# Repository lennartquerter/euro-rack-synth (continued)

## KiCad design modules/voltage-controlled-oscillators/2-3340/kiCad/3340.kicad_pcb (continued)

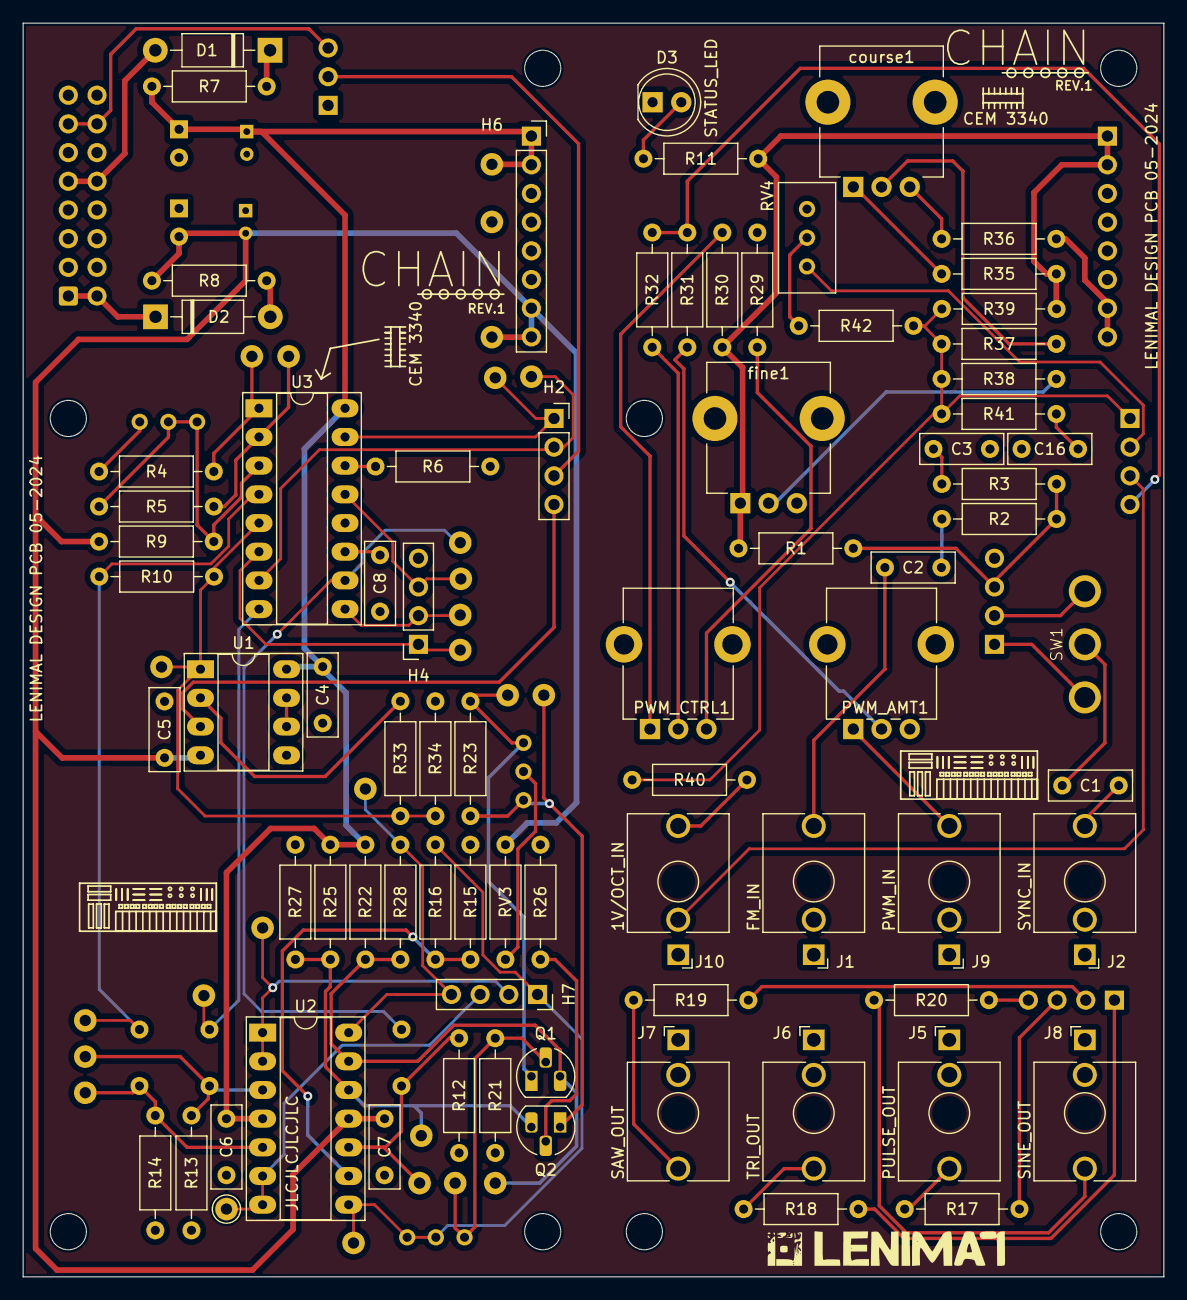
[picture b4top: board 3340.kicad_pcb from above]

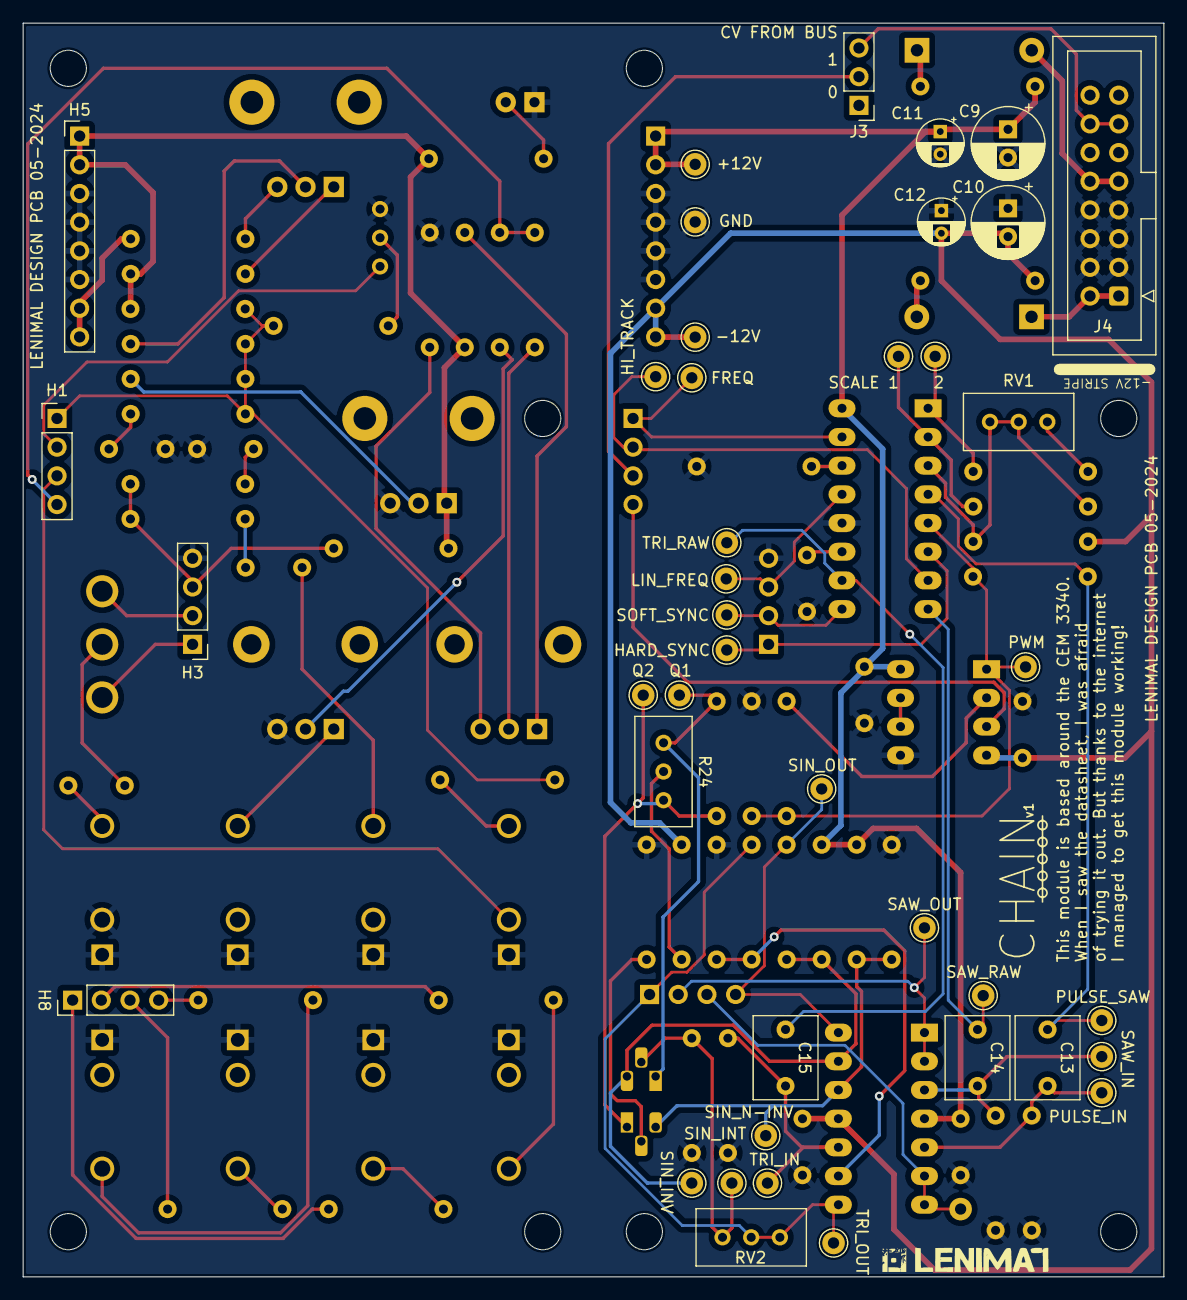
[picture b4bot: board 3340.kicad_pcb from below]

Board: 2 copper layers, 101.0 x 111.0 mm, 127 parts (41 on the bottom side), 75 nets.

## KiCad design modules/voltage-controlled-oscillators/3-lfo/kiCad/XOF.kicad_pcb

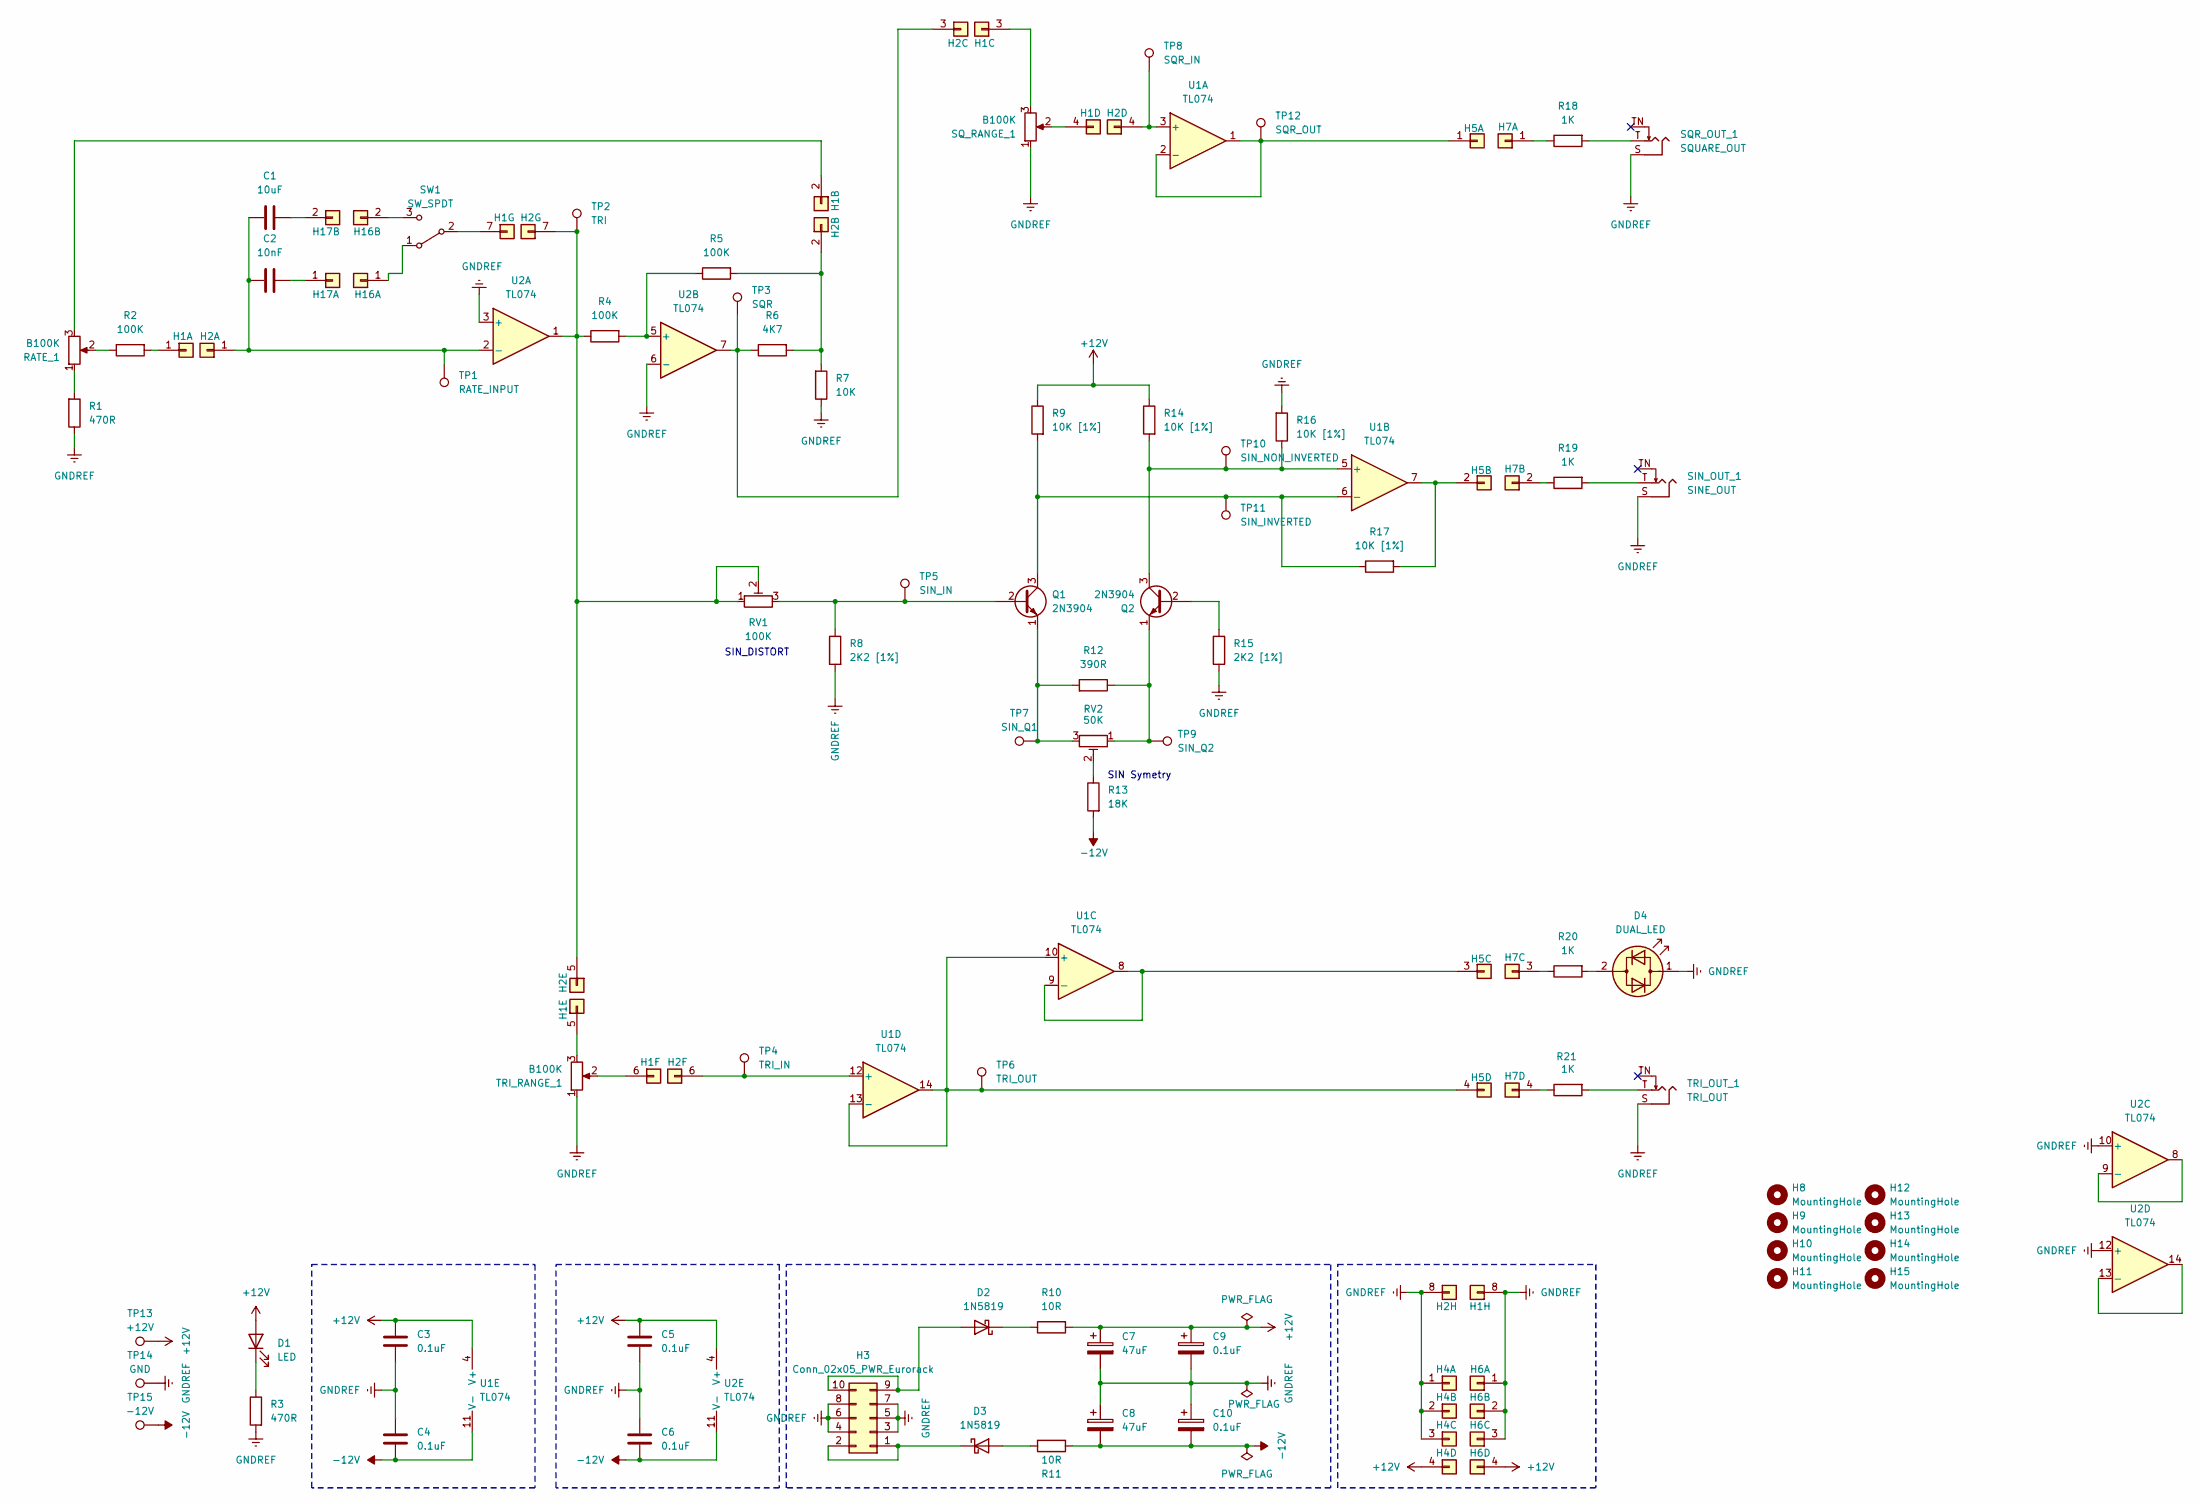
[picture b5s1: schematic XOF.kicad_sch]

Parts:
C1: 10uF; C_RECT_MKT_1uF
C2: 10nF; C_RECT_MKT_1uF
C3, C4, C5, C6: 0.1uF; C_Disc_D5.0mm_W2.5mm_P5.00mm
C7, C8: 47uF; CP_Radial_D6.3mm_P2.50mm
C9, C10: 0.1uF; CP_Radial_D4.0mm_P2.00mm
D1: LED; LED_D5.0mm (center Aligned)
D2, D3: 1N5819; D_DO-41_SOD81_P10.16mm_Horizontal
D4: DUAL_LED; LED_D5.0mm (center Aligned)
H1: PinHeader_01x08; PinHeader_1x08_P2.54mm_Vertical
H2: PinSocket_01x08; PinSocket_1x08_P2.54mm_Vertical
H3: Conn_02x05_PWR_Eurorack; IDC-Header_2x05_P2.54mm_Vertical
H4, H7: PinHeader_01x04; PinHeader_1x04_P2.54mm_Vertical
H5, H6: PinSocket_01x04; PinSocket_1x04_P2.54mm_Vertical
H8, H9, H10, H11, H12, H13, H14, H15: MountingHole; MountingHole_3.2mm_M3
H16: PinHeader_01x02; PinHeader_1x02_P2.54mm_Vertical
H17: PinSocket_01x02; PinSocket_1x02_P2.54mm_Vertical
Q1, Q2: 2N3904; TO-92_HandSolder
R1, R3: 470R; R_Default (DIN0207)
R2, R4, R5: 100K; R_Default (DIN0207)
R6: 4K7; R_Default (DIN0207)
R7: 10K; R_Default (DIN0207)
R8, R15: 2K2 [1%]; R_Default (DIN0207)
R9, R14, R16, R17: 10K [1%]; R_Default (DIN0207)
R10, R11: 10R; R_Default (DIN0207)
R12: 390R; R_Default (DIN0207)
R13: 18K; R_Default (DIN0207)
R18, R19, R20, R21: 1K; R_Default (DIN0207)
RATE_1: B100K; Potentiometer_TT_P0915N
RV1: 100K; Potentiometer_Bourns_3296W_Vertical
RV2: 50K; Potentiometer_Bourns_3296W_Vertical
SIN_OUT_1: SINE_OUT; Jack_3.5mm_QingPu_WQP-PJ398SM_Vertical_CircularHoles
SQR_OUT_1: SQUARE_OUT; Jack_3.5mm_QingPu_WQP-PJ398SM_Vertical_CircularHoles
SQ_RANGE_1: B100K; Potentiometer_TT_P0915N
SW1: SW_SPDT; SW_default
TP1: RATE_INPUT; Pin_D1.0mm_L10.0mm
TP2: TRI; Pin_D1.0mm_L10.0mm
TP3: SQR; Pin_D1.0mm_L10.0mm
TP4: TRI_IN; Pin_D1.0mm_L10.0mm
TP5: SIN_IN; Pin_D1.0mm_L10.0mm
TP6: TRI_OUT; Pin_D1.0mm_L10.0mm
TP7: SIN_Q1; Pin_D1.0mm_L10.0mm
TP8: SQR_IN; Pin_D1.0mm_L10.0mm
TP9: SIN_Q2; Pin_D1.0mm_L10.0mm
TP10: SIN_NON_INVERTED; Pin_D1.0mm_L10.0mm
TP11: SIN_INVERTED; Pin_D1.0mm_L10.0mm
TP12: SQR_OUT; Pin_D1.0mm_L10.0mm
TP13: +12V; Pin_D1.0mm_L10.0mm
TP14: GND; Pin_D1.0mm_L10.0mm
TP15: -12V; Pin_D1.0mm_L10.0mm
TRI_OUT_1: TRI_OUT; Jack_3.5mm_QingPu_WQP-PJ398SM_Vertical_CircularHoles
TRI_RANGE_1: B100K; Potentiometer_TT_P0915N
U1, U2: TL074; DIP-14_W7.62mm_Socket_LongPads

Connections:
+12V: C3.1, C5.1, C7.1, C9.1, D1.2 (A), H4.4, H6.4, R9.2, R10.1, R14.2, TP13.1, U1.4 (V+), U2.4 (V+)
-12V: C4.2, C6.2, C8.2, C10.2, R11.1, R13.1, TP15.1, U1.11 (V-), U2.11 (V-)
GNDREF: C3.2, C4.1, C5.2, C6.1, C7.2, C8.1, C9.2, C10.1, D4.1 (KA), H1.8, H2.8, H3.3, H3.4, H3.5, H3.6, H3.7, H3.8, H4.1, H4.2, H4.3, H6.1, H6.2, H6.3, R1.2, R3.1, R7.2, R8.1, R15.2, R16.1, SIN_OUT_1.S, SQR_OUT_1.S, SQ_RANGE_1.1, TP14.1, TRI_OUT_1.S, TRI_RANGE_1.1, U2.3 (+), U2.6 (-), U2.10 (+), U2.12 (+)
unnamed: D1.1 (K), R3.2
unnamed: D2.2 (A), H3.9, H3.10
unnamed: D2.1 (K), R10.2
unnamed: D3.2 (A), R11.2
unnamed: D3.1 (K), H3.1, H3.2
unnamed: D4.2 (AK), R20.1
unnamed: H1.1, R2.1
unnamed: H1.2, RATE_1.3
unnamed: H1.3, SQ_RANGE_1.3
unnamed: H1.4, SQ_RANGE_1.2
unnamed: H1.5, TRI_RANGE_1.3
unnamed: H1.6, TRI_RANGE_1.2
unnamed: H1.7, SW1.2 (B)
unnamed: C1.1, C2.1, H2.1 (Pin_3), TP1.1, U2.2 (-)
unnamed: H2.2, R5.1, R6.1, R7.1
unnamed: H2.3, R6.2, TP3.1, U2.7
unnamed: H2.4, TP8.1, U1.3 (+)
unnamed: H2.5, H2.7, R4.2, RV1.1, RV1.2, TP2.1, U2.1
unnamed: H2.6, TP4.1, U1.12 (+)
unnamed: H5.1, TP12.1, U1.1, U1.2 (-)
unnamed: H5.2, R17.1, U1.7
unnamed: H5.3, U1.8, U1.9 (-)
unnamed: H5.4, TP6.1, U1.10 (+), U1.13 (-), U1.14
unnamed: H7.1, R18.2
unnamed: H7.2, R19.2
unnamed: H7.3, R20.2
unnamed: H7.4, R21.2
unnamed: H16.1, SW1.1 (A)
unnamed: H16.2, SW1.3 (C)
unnamed: C2.2, H17.1
unnamed: C1.2, H17.2
unnamed: Q1.2 (B), R8.2, RV1.3, TP5.1
unnamed: Q1.3 (C), R9.1, R17.2, TP11.1, U1.6 (-)
unnamed: Q1.1 (E), R12.1, RV2.3, TP7.1
unnamed: Q2.2 (B), R15.1
unnamed: Q2.3 (C), R14.1, R16.2, TP10.1, U1.5 (+)
unnamed: Q2.1 (E), R12.2, RV2.1, TP9.1
unnamed: R1.1, RATE_1.1
unnamed: R2.2, RATE_1.2
unnamed: R13.2, RV2.2
unnamed: R18.1, SQR_OUT_1.T
unnamed: R19.1, SIN_OUT_1.T
unnamed: R21.1, TRI_OUT_1.T
unnamed: R4.1, R5.2, U2.5 (+)
unnamed: U2.8, U2.9 (-)
unnamed: U2.13 (-), U2.14

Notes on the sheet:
SIN Symetry
SIN_DISTORT

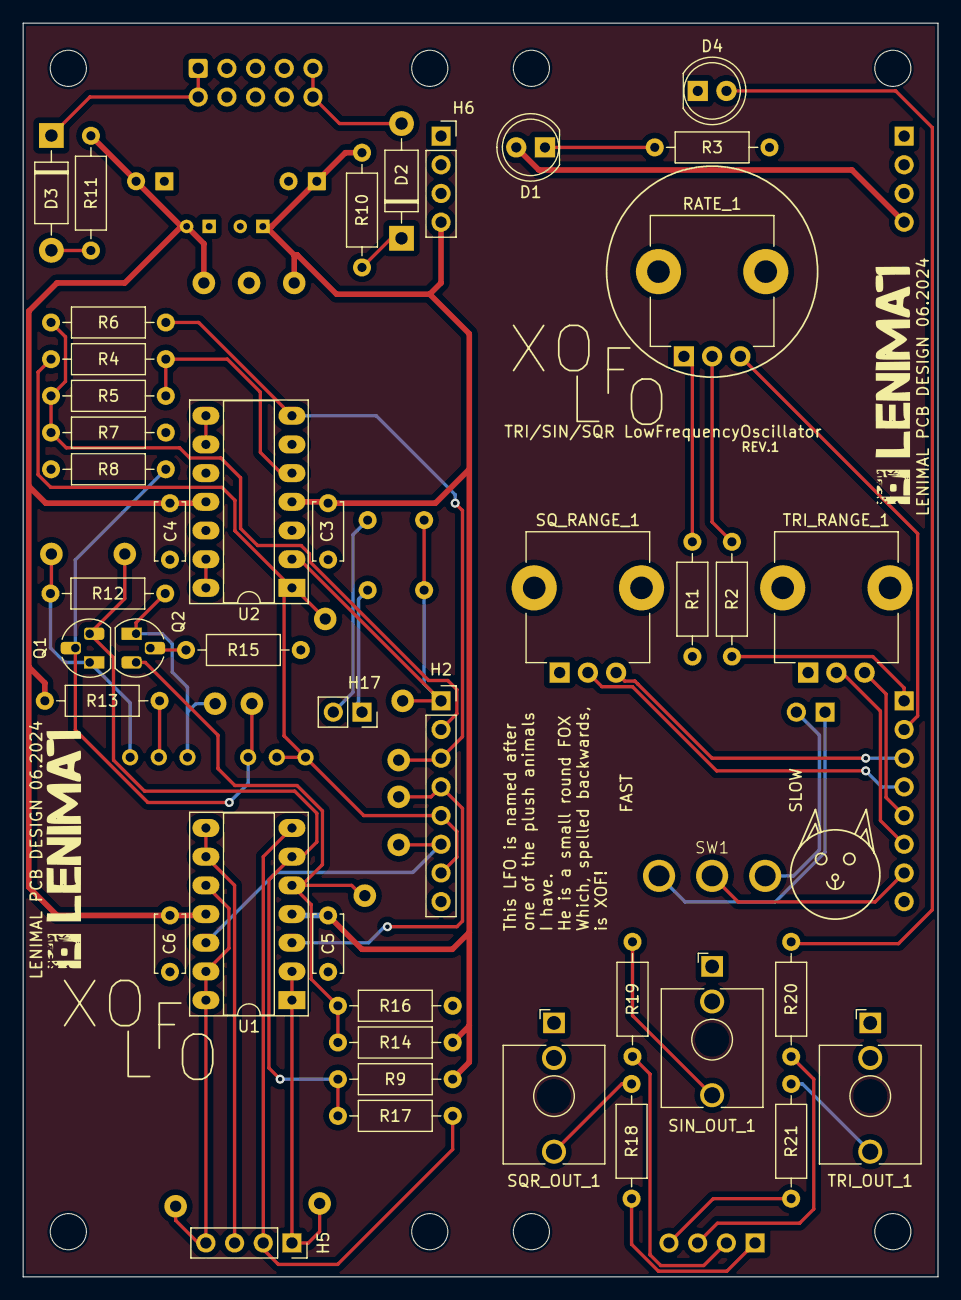
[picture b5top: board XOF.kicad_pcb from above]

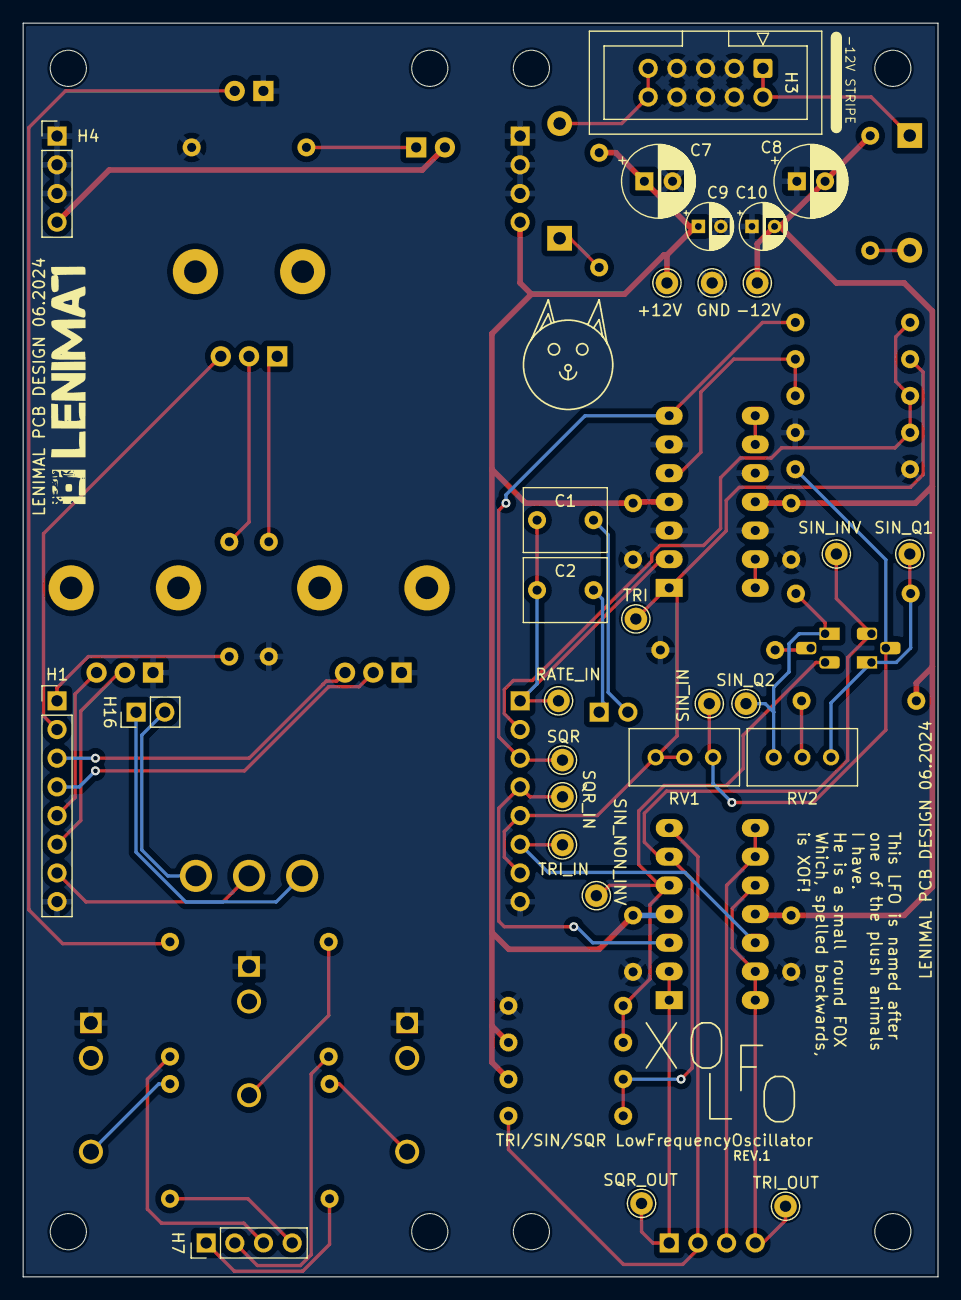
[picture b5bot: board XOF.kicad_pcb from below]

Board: 2 copper layers, 81.0 x 111.0 mm, 80 parts (28 on the bottom side), 49 nets.

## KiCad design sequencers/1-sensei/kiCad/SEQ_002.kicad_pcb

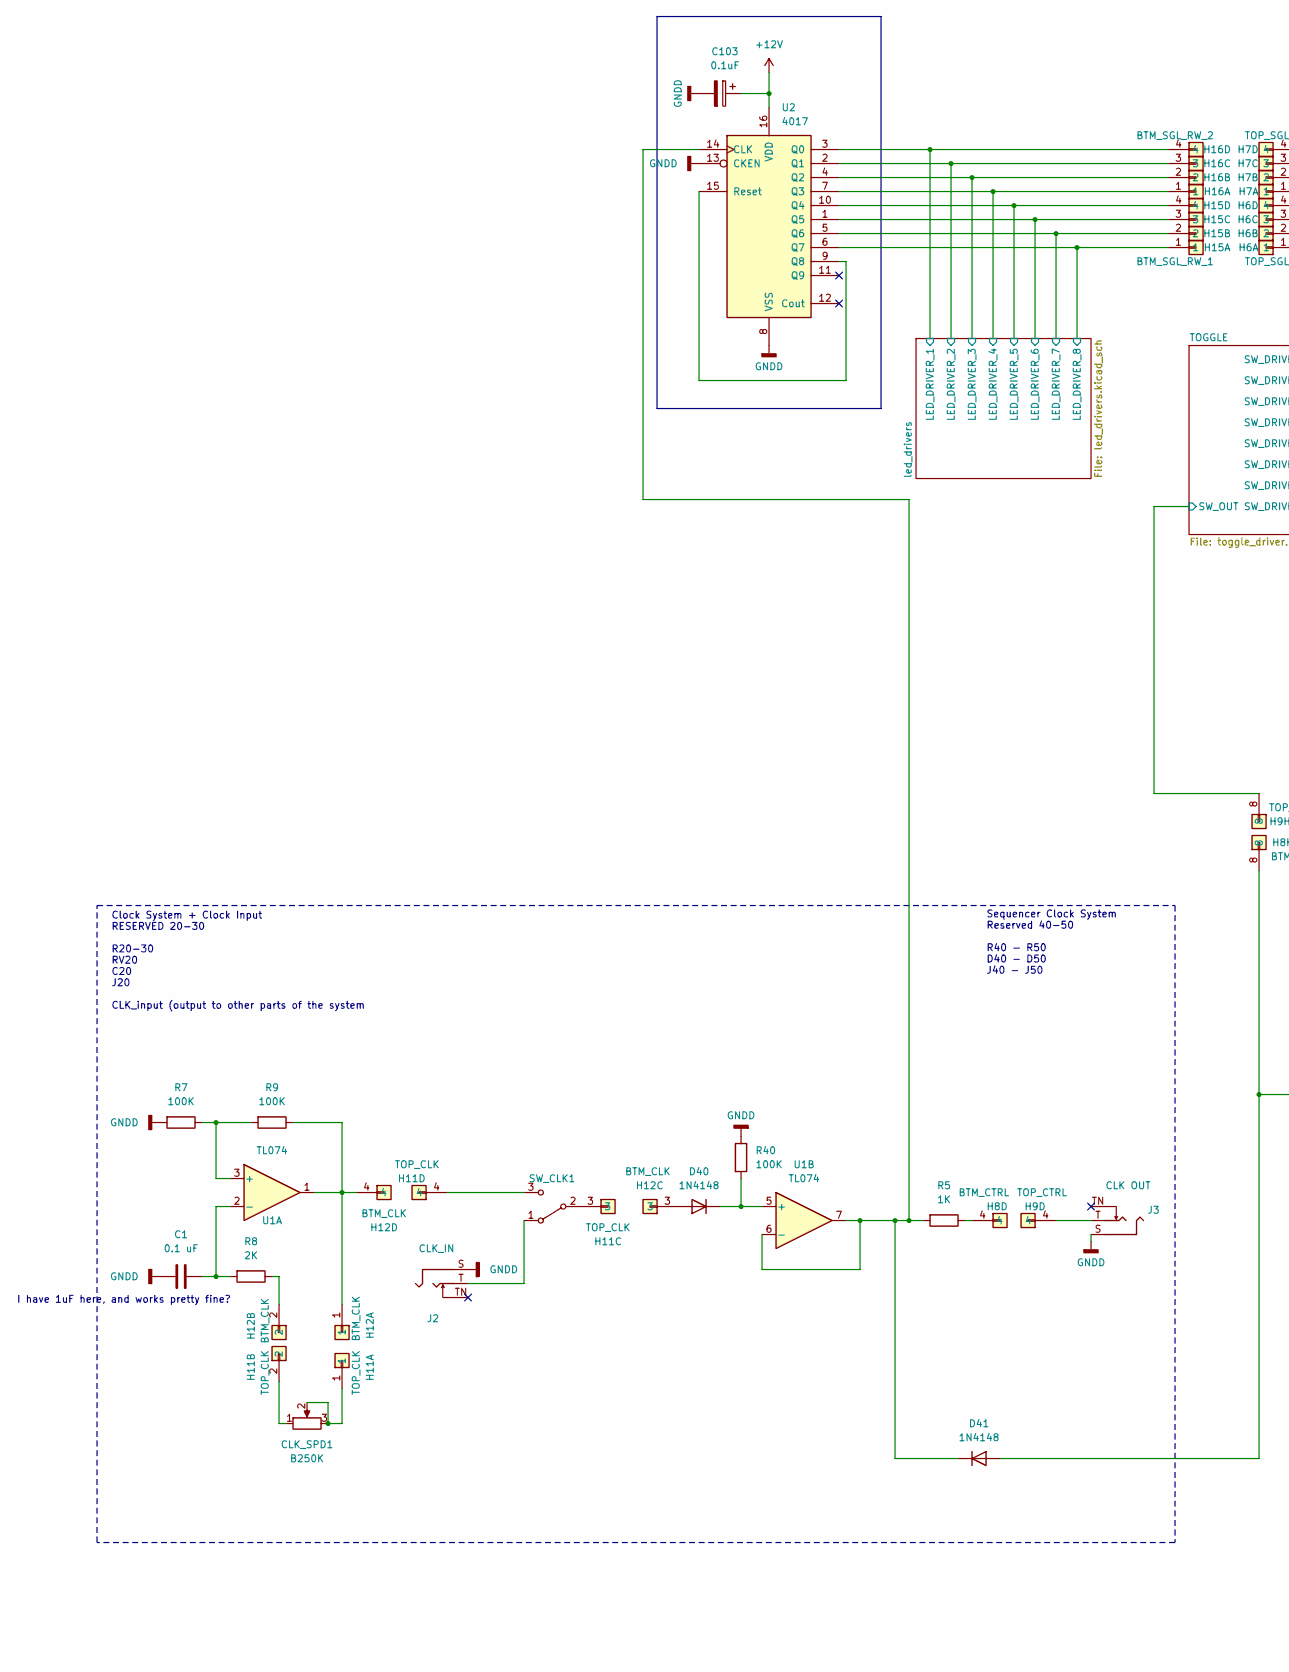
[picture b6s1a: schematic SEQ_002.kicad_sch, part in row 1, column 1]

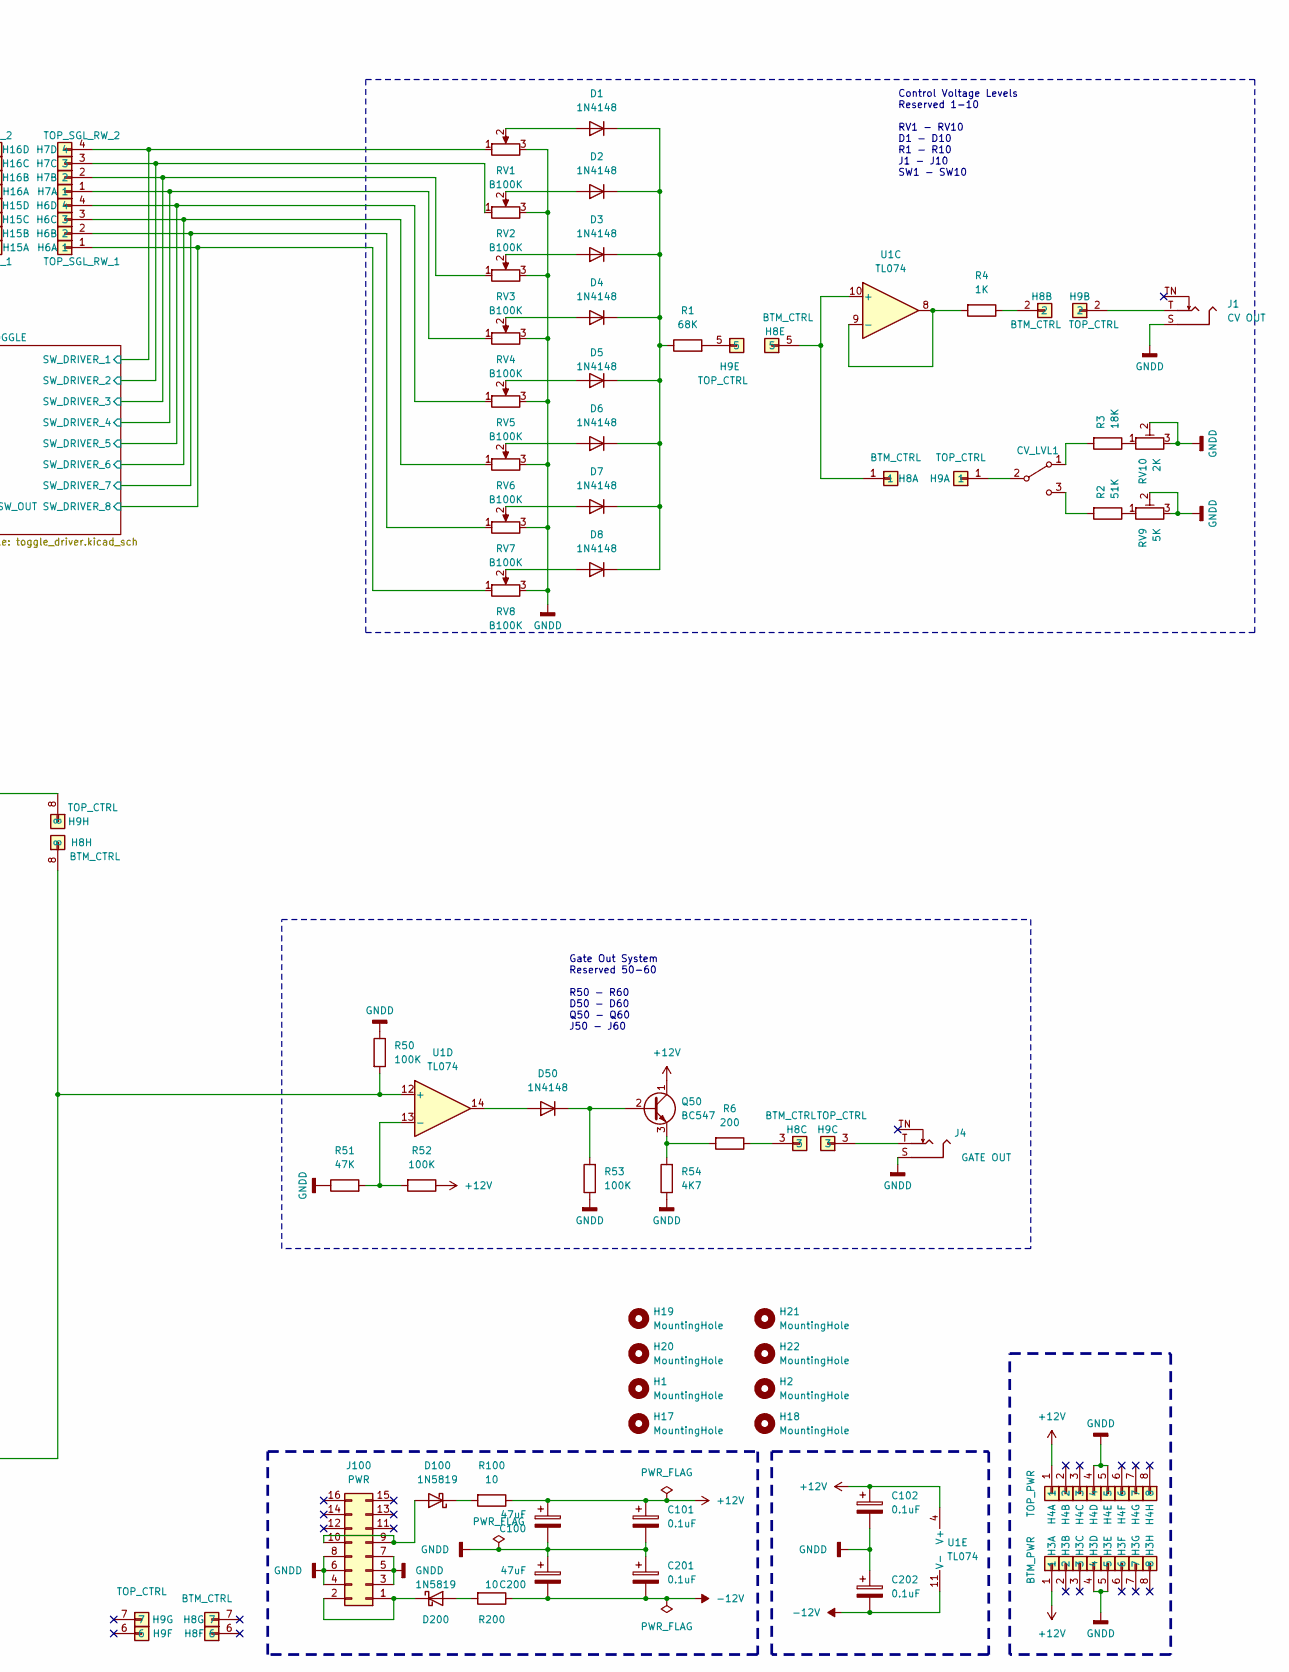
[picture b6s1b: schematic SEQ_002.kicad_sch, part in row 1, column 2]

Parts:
C1: 0.1 uF; C_Rect_L7.2mm_W3.5mm_P5.00mm_FKS2_FKP2_MKS2_MKP2
C100, C200: 47uF; CP_Radial_D5.0mm_P2.00mm
C101, C102, C103, C201, C202: 0.1uF; CP_Radial_D4.0mm_P2.00mm
CLK_SPD1: B250K; Potentiometer_TT_P0915N
CV_LVL1: SPDT_Toggle
D1, D2, D3, D4, D5, D6, D7, D8, D40, D41, D50: 1N4148; D_DO-35_SOD27_P7.62mm_Horizontal
D100, D200: 1N5819; D_DO-35_SOD27_P7.62mm_Horizontal
H1, H2, H17, H18, H19, H20, H21, H22: MountingHole; MountingHole_3.5mm
H3: BTM_PWR; PinSocket_1x08_P2.00mm_Vertical
H4: TOP_PWR; PinHeader_1x08_P2.00mm_Vertical
H6: TOP_SGL_RW_1; PinHeader_1x04_P2.00mm_Vertical
H7: TOP_SGL_RW_2; PinHeader_1x04_P2.00mm_Vertical
H8: BTM_CTRL; PinSocket_1x08_P2.00mm_Vertical
H9: TOP_CTRL; PinHeader_1x08_P2.00mm_Vertical
H11: TOP_CLK; PinHeader_1x04_P2.00mm_Vertical
H12: BTM_CLK; PinSocket_1x04_P2.00mm_Vertical
H15: BTM_SGL_RW_1; PinSocket_1x04_P2.00mm_Vertical
H16: BTM_SGL_RW_2; PinSocket_1x04_P2.00mm_Vertical
J1: CV OUT; Jack_3.5mm_QingPu_WQP-PJ398SM_Vertical_CircularHoles
J2: CLK_IN; Jack_3.5mm_QingPu_WQP-PJ398SM_Vertical_CircularHoles
J3: CLK OUT; Jack_3.5mm_QingPu_WQP-PJ398SM_Vertical_CircularHoles
J4: GATE OUT; Jack_3.5mm_QingPu_WQP-PJ398SM_Vertical_CircularHoles
J100: PWR; CONN_02x08_PWR
Q50: BC547; TO-92_Inline
R1: 68K; R_Axial_DIN0207_L6.3mm_D2.5mm_P10.16mm_Horizontal
R2: 51K; R_Axial_DIN0207_L6.3mm_D2.5mm_P10.16mm_Horizontal
R3: 18K; R_Axial_DIN0207_L6.3mm_D2.5mm_P10.16mm_Horizontal
R4, R5: 1K; R_Axial_DIN0207_L6.3mm_D2.5mm_P10.16mm_Horizontal
R6: 200; R_Axial_DIN0207_L6.3mm_D2.5mm_P10.16mm_Horizontal
R7, R9, R40, R50, R52, R53: 100K; R_Axial_DIN0207_L6.3mm_D2.5mm_P10.16mm_Horizontal
R8: 2K; R_Axial_DIN0207_L6.3mm_D2.5mm_P10.16mm_Horizontal
R51: 47K; R_Axial_DIN0207_L6.3mm_D2.5mm_P10.16mm_Horizontal
R54: 4K7; R_Axial_DIN0207_L6.3mm_D2.5mm_P10.16mm_Horizontal
R100, R200: 10; R_Axial_DIN0207_L6.3mm_D2.5mm_P10.16mm_Horizontal
RV1, RV2, RV3, RV4, RV5, RV6, RV7, RV8: B100K; Potentiometer_TT_P0915N
RV9: 5K; Potentiometer_Bourns_3296W_Vertical
RV10: 2K; Potentiometer_Bourns_3296W_Vertical
SW_CLK1: SPDT_Toggle
U1: TL074; DIP-14_W7.62mm_Socket_LongPads
U2: 4017; DIP-16_W7.62mm_Socket_LongPads

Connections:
+12V: C100.1, C101.1, C102.1, C103.1, H3.1, H4.1, Q50.1 (C), R52.1, R100.1, U1.4 (V+), U2.16 (VDD); also elsewhere on the board
-12V: C200.2, C201.2, C202.2, R200.1, U1.11 (V-)
/TOGGLE/SW_DRIVER_1: H7.4, RV1.1; also elsewhere on the board
/TOGGLE/SW_DRIVER_2: H7.3, RV2.1; also elsewhere on the board
/TOGGLE/SW_DRIVER_3: H7.2, RV3.1; also elsewhere on the board
/TOGGLE/SW_DRIVER_4: H7.1, RV4.1; also elsewhere on the board
/TOGGLE/SW_DRIVER_5: H6.4, RV5.1; also elsewhere on the board
/TOGGLE/SW_DRIVER_6: H6.3, RV6.1; also elsewhere on the board
/TOGGLE/SW_DRIVER_7: H6.2, RV7.1; also elsewhere on the board
/TOGGLE/SW_DRIVER_8: H6.1, RV8.1; also elsewhere on the board
/TOGGLE/SW_OUT: H9.8; also elsewhere on the board
/led_drivers/LED_DRIVER_1: H16.4, U2.3 (Q0); also elsewhere on the board
/led_drivers/LED_DRIVER_2: H16.3, U2.2 (Q1); also elsewhere on the board
/led_drivers/LED_DRIVER_3: H16.2, U2.4 (Q2); also elsewhere on the board
/led_drivers/LED_DRIVER_4: H16.1, U2.7 (Q3); also elsewhere on the board
/led_drivers/LED_DRIVER_5: H15.4, U2.10 (Q4); also elsewhere on the board
/led_drivers/LED_DRIVER_6: H15.3, U2.1 (Q5); also elsewhere on the board
/led_drivers/LED_DRIVER_7: H15.2, U2.5 (Q6); also elsewhere on the board
/led_drivers/LED_DRIVER_8: H15.1, U2.6 (Q7); also elsewhere on the board
GNDD: C1.1, C100.2, C101.2, C102.2, C103.2, C200.1, C201.1, C202.1, H3.4, H3.5, H4.4, H4.5, J1.S, J2.S, J3.S, J4.S, J100.3 (GND), J100.4 (GND), J100.5 (GND), J100.6 (GND), J100.7 (GND), J100.8 (GND), R7.2, R40.1, R50.1, R51.1, R53.1, R54.1, RV1.3, RV2.3, RV3.3, RV4.3, RV5.3, RV6.3, RV7.3, RV8.3, RV9.2, RV9.3, RV10.2, RV10.3, U2.8 (VSS), U2.13 (CKEN); also elsewhere on the board
unnamed: CLK_SPD1.1, H11.2
unnamed: CLK_SPD1.2, CLK_SPD1.3, H11.1
unnamed: CV_LVL1.1 (A), R3.2
unnamed: CV_LVL1.2 (B), H9.1
unnamed: CV_LVL1.3 (C), R2.2
unnamed: D1.2 (A), RV1.2
unnamed: D1.1 (K), D2.1 (K), D3.1 (K), D4.1 (K), D5.1 (K), D6.1 (K), D7.1 (K), D8.1 (K), R1.1
unnamed: D2.2 (A), RV2.2
unnamed: D3.2 (A), RV3.2
unnamed: D4.2 (A), RV4.2
unnamed: D5.2 (A), RV5.2
unnamed: D6.2 (A), RV6.2
unnamed: D7.2 (A), RV7.2
unnamed: D8.2 (A), RV8.2
unnamed: D40.2 (A), H12.3
unnamed: D40.1 (K), R40.2, U1.5 (+)
unnamed: D41.2 (A), H8.8, R50.2, U1.12 (+)
unnamed: D41.1 (K), R5.2, U1.6 (-), U1.7, U2.14 (CLK)
unnamed: D50.2 (A), U1.14
unnamed: D50.1 (K), Q50.2 (B), R53.2
unnamed: D100.2 (A), J100.9 (+12V), J100.10 (+12V)
unnamed: D100.1 (K), R100.2
unnamed: D200.2 (A), R200.2
unnamed: D200.1 (K), J100.1 (-12V), J100.2 (-12V)
unnamed: H8.2, R4.1
unnamed: H8.3, R6.1
unnamed: H8.4, R5.1
unnamed: H9.2, J1.T
unnamed: H9.3, J4.T
unnamed: H9.4, J3.T
unnamed: H9.5, R1.2
unnamed: H12.1, H12.4, R9.1, U1.1
unnamed: H12.2, R8.1
unnamed: Q50.3 (E), R6.2, R54.2
unnamed: R2.1, RV9.1
unnamed: R3.1, RV10.1
unnamed: J2.T, SW_CLK1.1 (A)
unnamed: H11.3, SW_CLK1.2 (B)
unnamed: H11.4, SW_CLK1.3 (C)
unnamed: R7.1, R9.2, U1.3 (+)
unnamed: C1.2, R8.2, U1.2 (-)
unnamed: H8.1, H8.5, U1.10 (+)
unnamed: R4.2, U1.8, U1.9 (-)
unnamed: R51.2, R52.2, U1.13 (-)
unnamed: U2.9 (Q8), U2.15 (Reset)

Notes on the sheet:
Sequencer Clock System Reserved 40-50 R40 - R50 D40 - D50 J40 - J50
Clock System + Clock Input RESERVED 20-30 R20-30 RV20 C20 J20 CLK_input (output to other parts of the system
I have 1uF here, and works pretty fine?
Control Voltage Levels Reserved 1-10 RV1 - RV10 D1 - D10 R1 - R10 J1 - J10 SW1 - SW10
Gate Out System Reserved 50-60 R50 - R60 D50 - D60 Q50 - Q60 J50 - J60

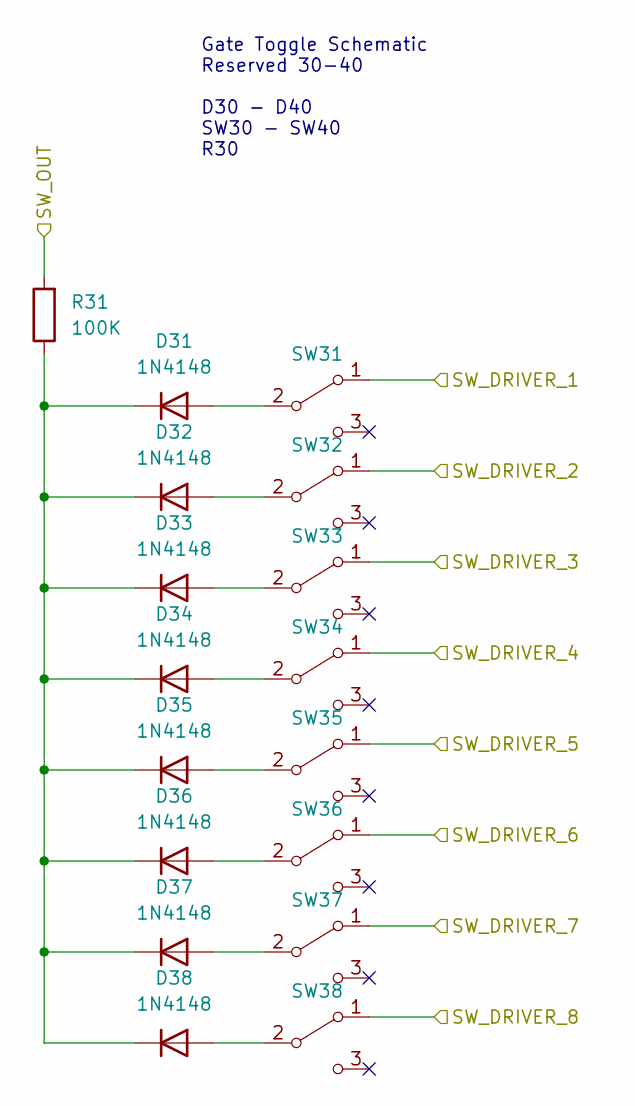
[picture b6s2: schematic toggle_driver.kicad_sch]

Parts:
D31, D32, D33, D34, D35, D36, D37, D38: 1N4148; D_DO-35_SOD27_P7.62mm_Horizontal
R31: 100K; R_Axial_DIN0207_L6.3mm_D2.5mm_P10.16mm_Horizontal
SW31, SW32, SW33, SW34, SW35, SW36, SW37, SW38: SPDT_Toggle

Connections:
/TOGGLE/SW_DRIVER_1: SW31.1 (A); also elsewhere on the board
/TOGGLE/SW_DRIVER_2: SW32.1 (A); also elsewhere on the board
/TOGGLE/SW_DRIVER_3: SW33.1 (A); also elsewhere on the board
/TOGGLE/SW_DRIVER_4: SW34.1 (A); also elsewhere on the board
/TOGGLE/SW_DRIVER_5: SW35.1 (A); also elsewhere on the board
/TOGGLE/SW_DRIVER_6: SW36.1 (A); also elsewhere on the board
/TOGGLE/SW_DRIVER_7: SW37.1 (A); also elsewhere on the board
/TOGGLE/SW_DRIVER_8: SW38.1 (A); also elsewhere on the board
/TOGGLE/SW_OUT: R31.2; also elsewhere on the board
unnamed: D31.2 (A), SW31.2 (B)
unnamed: D31.1 (K), D32.1 (K), D33.1 (K), D34.1 (K), D35.1 (K), D36.1 (K), D37.1 (K), D38.1 (K), R31.1
unnamed: D32.2 (A), SW32.2 (B)
unnamed: D33.2 (A), SW33.2 (B)
unnamed: D34.2 (A), SW34.2 (B)
unnamed: D35.2 (A), SW35.2 (B)
unnamed: D36.2 (A), SW36.2 (B)
unnamed: D37.2 (A), SW37.2 (B)
unnamed: D38.2 (A), SW38.2 (B)

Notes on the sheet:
Gate Toggle Schematic Reserved 30-40 D30 - D40 SW30 - SW40 R30
